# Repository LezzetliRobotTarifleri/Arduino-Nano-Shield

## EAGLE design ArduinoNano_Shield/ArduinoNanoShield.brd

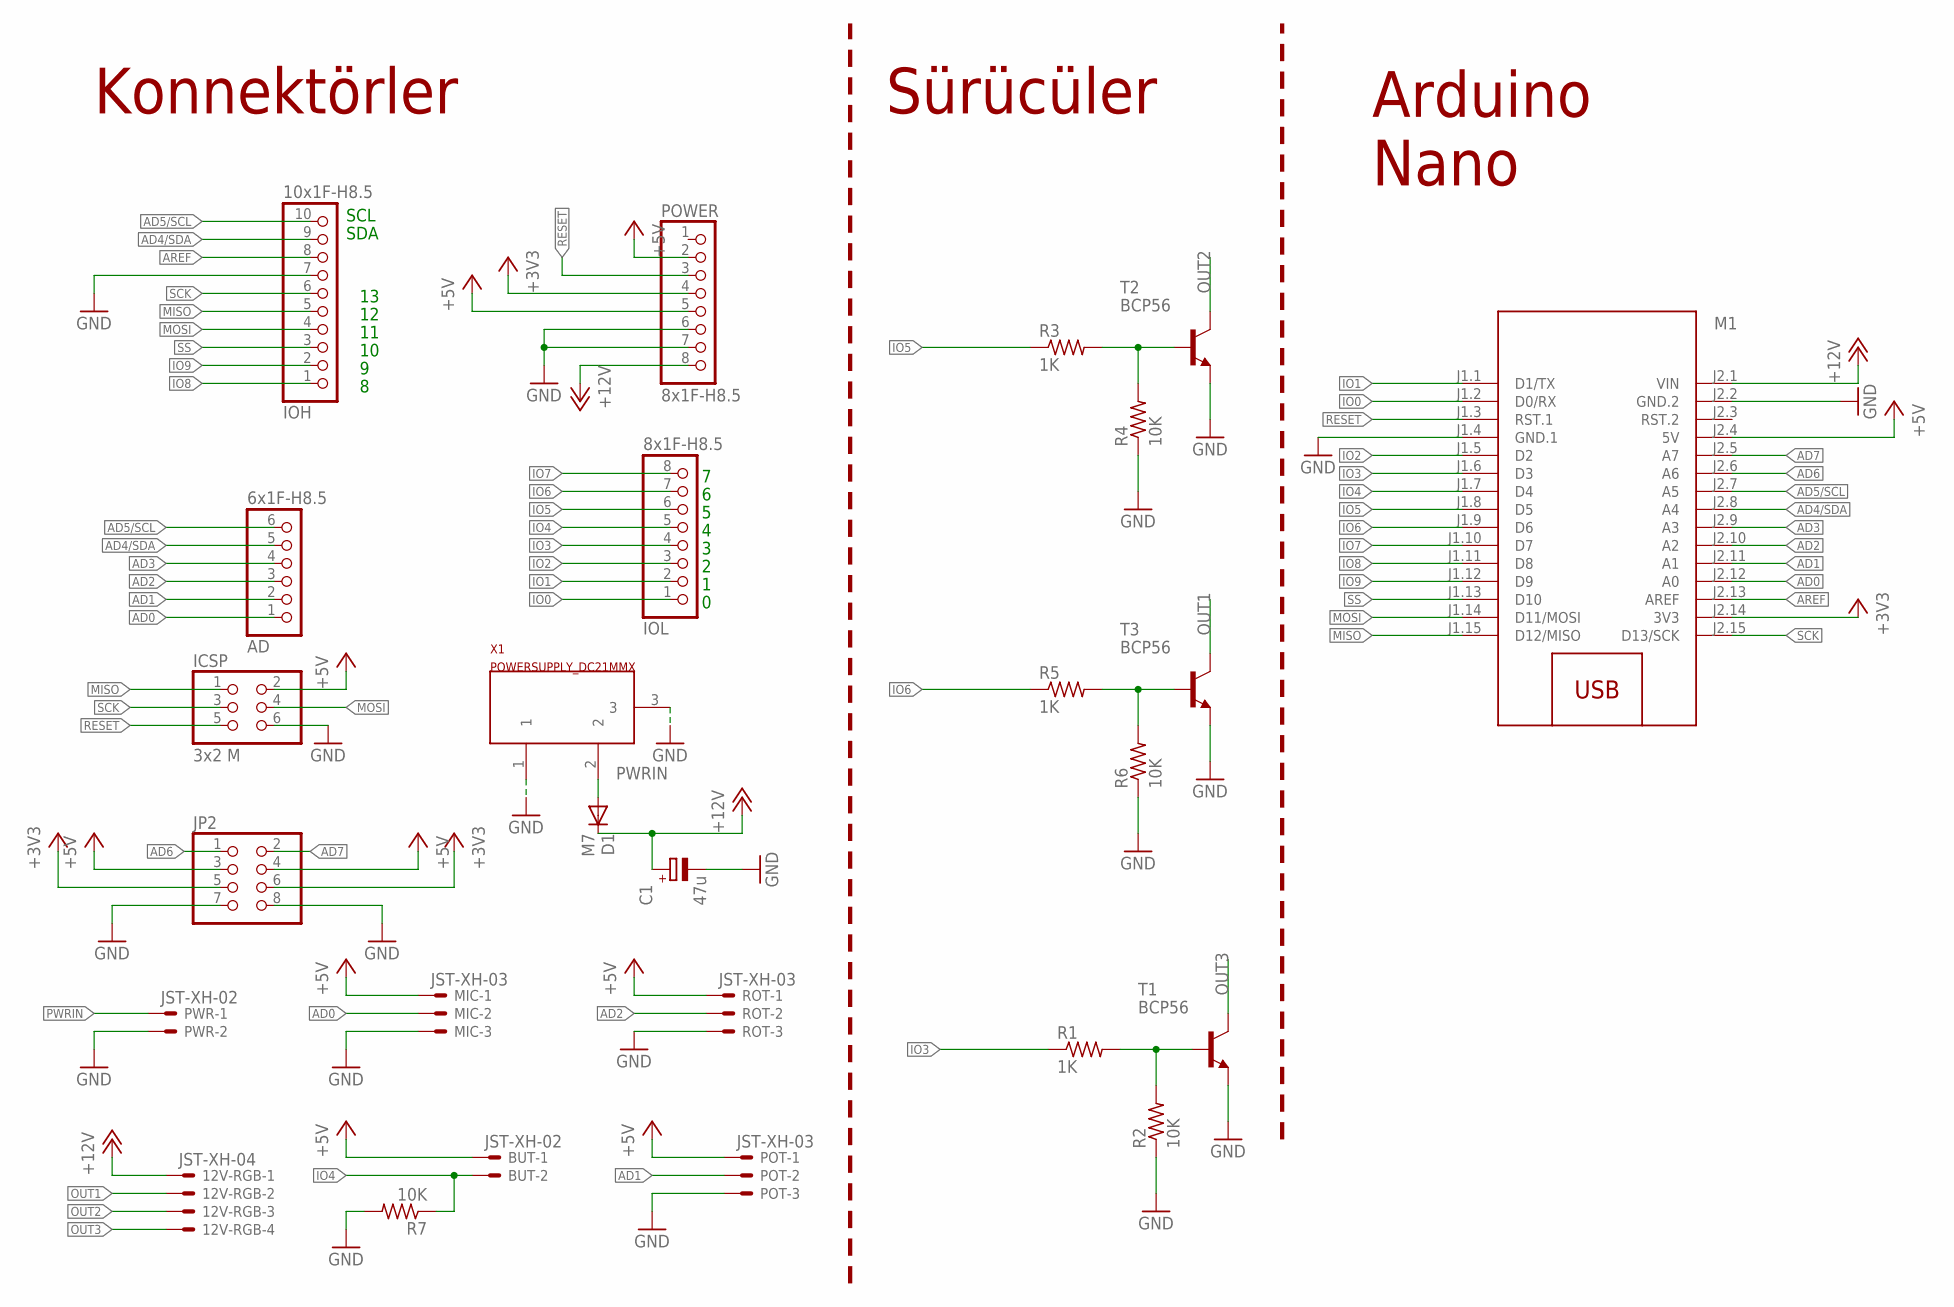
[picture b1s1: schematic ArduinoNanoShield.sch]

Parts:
12V-RGB: JST-XH-04; JST-XH-04-PACKAGE-ROUND-PAD
AD: 6x1F-H8.5; 1X06
BUT: JST-XH-02; JST-XH-02-PACKAGE-ROUND-PAD
C1: 47u; PANASONIC_D
D1: M7; SMB
ICSP: 3x2 M; 2X03
IOH: 10x1F-H8.5; 1X10
IOL: 8x1F-H8.5; 1X08
JP2: PINHD-2X4; 2X04
M1: ARDUINO-NANO
MIC: JST-XH-03; JST-XH-03-PACKAGE-ROUND-PAD
POT: JST-XH-03; JST-XH-03-PACKAGE-ROUND-PAD
POWER: 8x1F-H8.5; 1X08
PWR: JST-XH-02; JST-XH-02-PACKAGE-ROUND-PAD
R1, R3, R5: 1K; M0805
R2, R4, R6, R7: 10K; M0805
ROT: JST-XH-03; JST-XH-03-PACKAGE-ROUND-PAD
T1, T2, T3: BCP56; SOT223
X1: POWERSUPPLY_DC21MMX; POWERSUPPLY_DC-21MM

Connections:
+3V3: JP2.5, JP2.6, M1.J2.14 (3V3), POWER.4
+5V: BUT.1, ICSP.2, JP2.3, JP2.4, M1.J2.4 (5V), MIC.1, POT.1, POWER.2, POWER.5, ROT.1
+12V: 12V-RGB.1, C1.+, D1.C, M1.J2.1 (VIN), POWER.8
AD0: AD.1, M1.J2.12 (A0), MIC.2
AD1: AD.2, M1.J2.11 (A1), POT.2
AD2: AD.3, M1.J2.10 (A2), ROT.2
AD3: AD.4, M1.J2.9 (A3)
AD4/SDA: AD.5, IOH.9, M1.J2.8 (A4)
AD5/SCL: AD.6, IOH.10, M1.J2.7 (A5)
AD6: JP2.1, M1.J2.6 (A6)
AD7: JP2.2, M1.J2.5 (A7)
AREF: IOH.8, M1.J2.13 (AREF)
GND: C1.-, ICSP.6, IOH.7, JP2.7, JP2.8, M1.J1.4 (GND.1), M1.J2.2 (GND.2), MIC.3, POT.3, POWER.6, POWER.7, PWR.2, R2.1, R4.1, R6.1, R7.2, ROT.3, T1.3 (E), T2.3 (E), T3.3 (E), X1.1, X1.3
IO0: IOL.1, M1.J1.2 (D0/RX)
IO1: IOL.2, M1.J1.1 (D1/TX)
IO2: IOL.3, M1.J1.5 (D2)
IO3: IOL.4, M1.J1.6 (D3), R1.1
IO4: BUT.2, IOL.5, M1.J1.7 (D4), R7.1
IO5: IOL.6, M1.J1.8 (D5), R3.1
IO6: IOL.7, M1.J1.9 (D6), R5.1
IO7: IOL.8, M1.J1.10 (D7)
IO8: IOH.1, M1.J1.11 (D8)
IO9: IOH.2, M1.J1.12 (D9)
MISO: ICSP.1, IOH.5, M1.J1.15 (D12/MISO)
MOSI: ICSP.4, IOH.4, M1.J1.14 (D11/MOSI)
unnamed: R1.2, R2.2, T1.1 (B)
unnamed: R3.2, R4.2, T2.1 (B)
unnamed: R5.2, R6.2, T3.1 (B)
OUT1: 12V-RGB.2, T3.4 (C)
OUT2: 12V-RGB.3, T2.4 (C)
OUT3: 12V-RGB.4, T1.4 (C)
PWRIN: D1.A, PWR.1, X1.2
RESET: ICSP.5, M1.J1.3 (RST.1), POWER.3
SCK: ICSP.3, IOH.6, M1.J2.15 (D13/SCK)
SS: IOH.3, M1.J1.13 (D10)

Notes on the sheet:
SDA
SCL
Konnektörler
Sürücüler
Arduino Nano

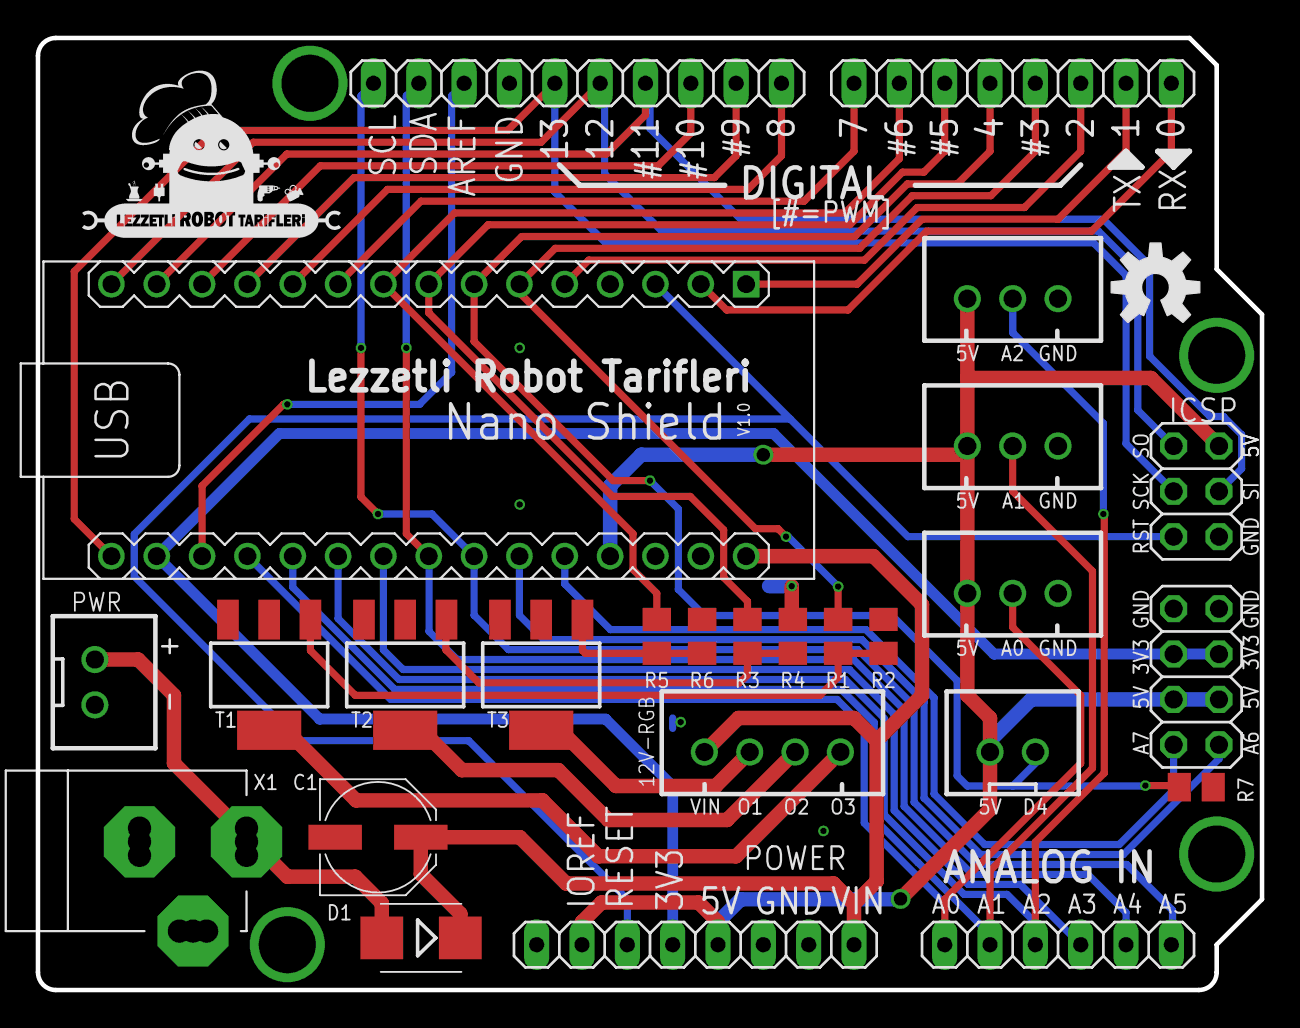
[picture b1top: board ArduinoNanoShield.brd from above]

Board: 2 copper layers, 68.6 x 53.3 mm, 29 parts (1 on the bottom side), 35 nets.

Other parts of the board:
U$1: LRT-LOGO-0,0125-B
U$2: OSHW-LOGO-M
U$4: LRT-LOGO-0,10416-B-N_I

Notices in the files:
parts and their libraries:
SparkFun-Aesthetics: Licensing: Creative Commons ShareAlike 4.0 International - https://creativecommons.org/licenses/by-sa/4.0
